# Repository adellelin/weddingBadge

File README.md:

# WeddingBadge
Designing a radio connected badge for wedding

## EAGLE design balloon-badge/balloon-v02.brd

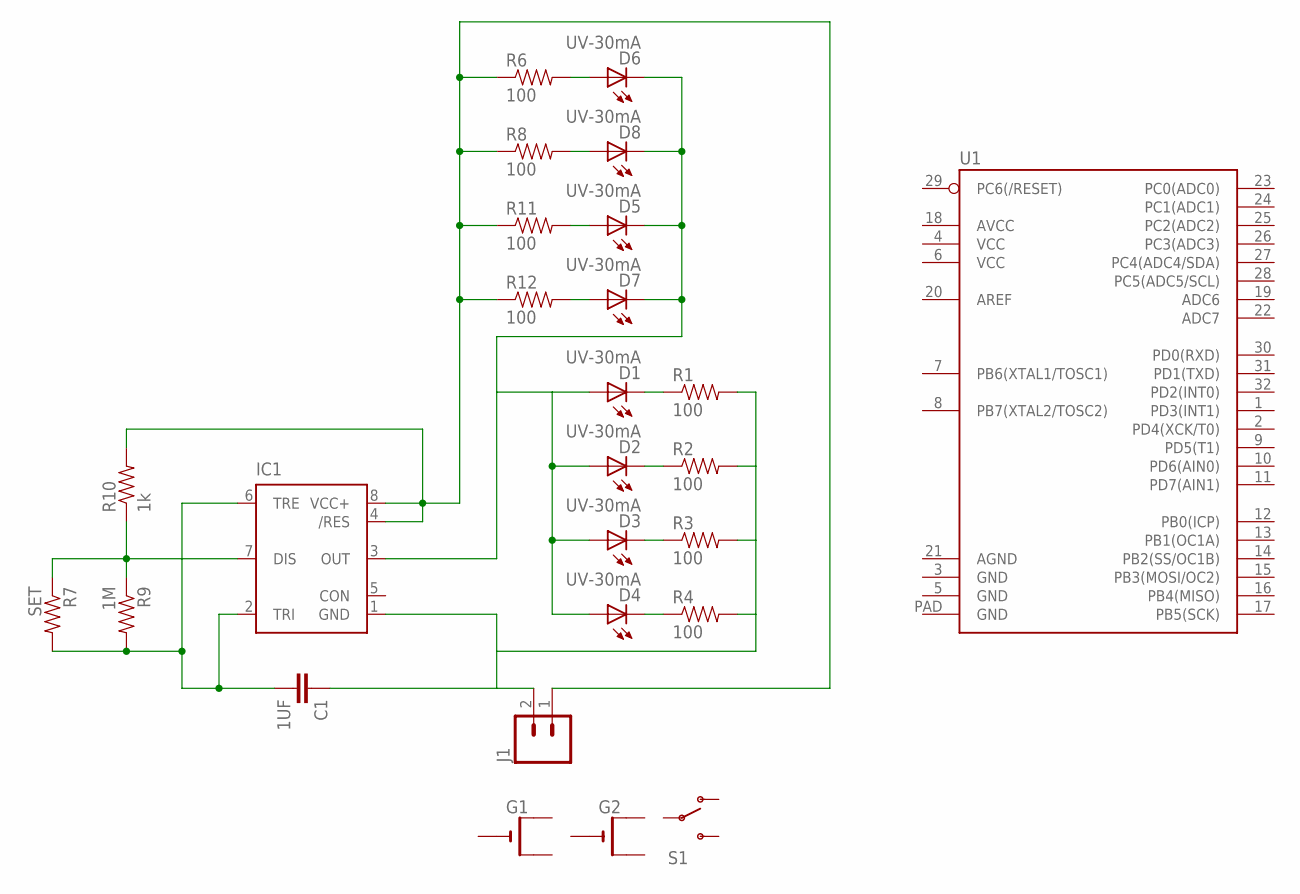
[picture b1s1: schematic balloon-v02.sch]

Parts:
C1: 1UF; 0603-CAP; DIGIKEY_PART_ID 1276-1946-1-ND
D1, D2, D3, D4, D5, D6, D7, D8: UV-30mA; CHIPLED_0603
G1, G2: CR2032SMT; CR2032-SMD; DIGIKEY_PART_ID BK-913-ND
IC1: NE555D; SO08; DIGIKEY_PART_ID ICM7555CBAZ-TCT-ND
J1: M02PTH3; 1X02_LONGPADS
R1, R2, R3, R4, R6, R8, R11, R12: 100; 0603-RES; DIGIKEY_PART_ID P100BZCT-ND
R7: SET; AXIAL-0.3-KIT; DIGIKEY_PART_ID P1MBZCT-ND
R9: 1M; 0603-RES; DIGIKEY_PART_ID P1MBZCT-ND
R10: 1k; 0603-RES; DIGIKEY_PART_ID P1KBZCT-ND
S1: SWITCH-SPDT-SMD-A; SWITCH-SPST-SMD-A; DIGIKEY_PART_ID 679-1847-1-ND
U1: ATMEGA328P_MLFMLF32; MLF32-PAD

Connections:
DISCHARGE: IC1.7 (DIS), R7.P$1 (1), R9.1, R10.1
GND: C1.1, IC1.1 (GND), J1.2, R1.2, R2.2, R3.2, R4.2
unnamed: D8.A, R8.2
unnamed: D5.A, R11.2
unnamed: D1.C, R1.1
unnamed: D7.A, R12.2
unnamed: D2.C, R2.1
unnamed: D6.A, R6.2
unnamed: D3.C, R3.1
unnamed: D4.C, R4.1
OUT: D1.A, D2.A, D3.A, D4.A, D5.C, D6.C, D7.C, D8.C, IC1.3 (OUT)
THRESHOLD: C1.2, IC1.2 (TRI), IC1.6 (TRE), R7.P$2 (2), R9.2
VCC: IC1.4 (/RES), IC1.8 (VCC+), J1.1, R6.1, R8.1, R10.2, R11.1, R12.1

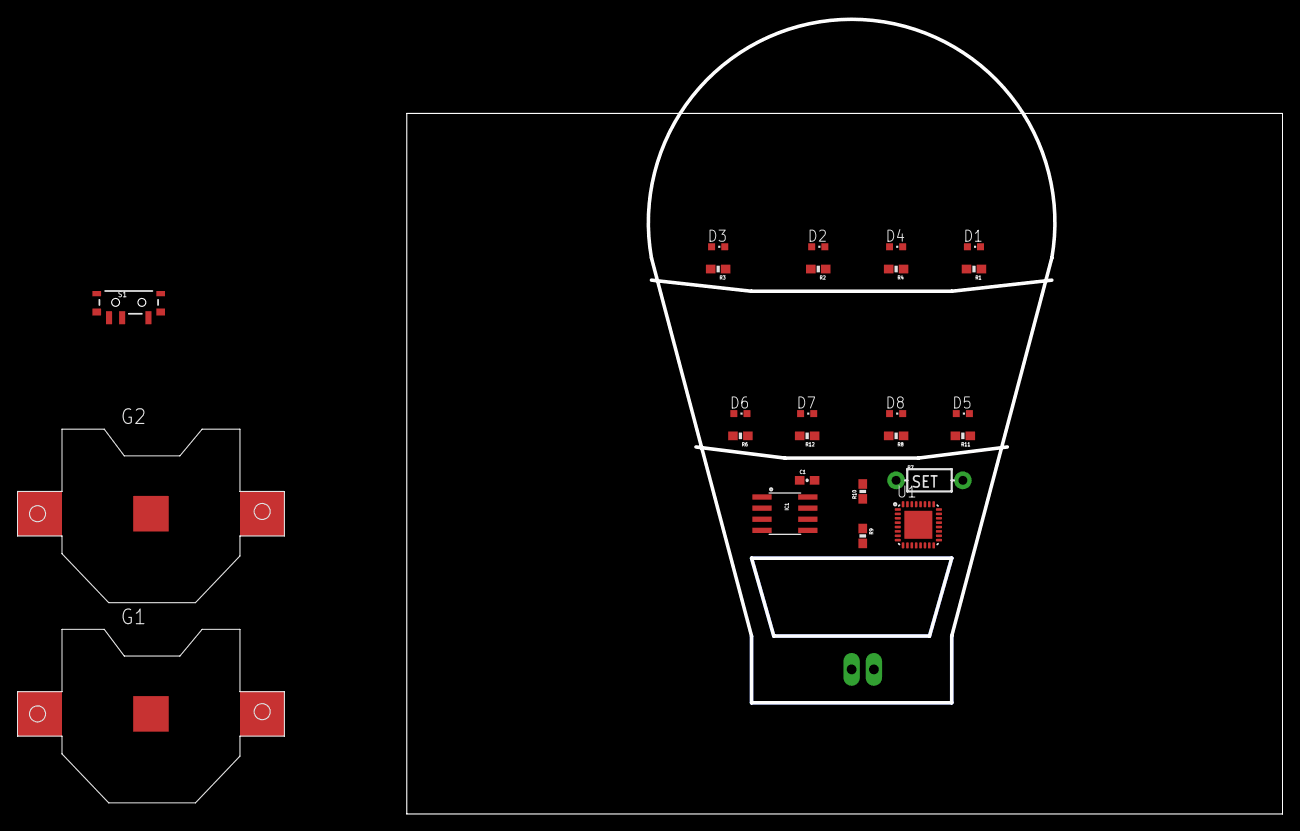
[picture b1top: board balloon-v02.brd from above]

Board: 2 copper layers, 100.0 x 90.7 mm, 26 parts (0 on the bottom side), 13 nets.

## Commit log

2019-10-12 added initial balloon outline

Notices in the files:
parts and their libraries:
SparkFun-Capacitors: Licensing: Creative Commons ShareAlike 4.0 International - https://creativecommons.org/licenses/by-sa/4.0
